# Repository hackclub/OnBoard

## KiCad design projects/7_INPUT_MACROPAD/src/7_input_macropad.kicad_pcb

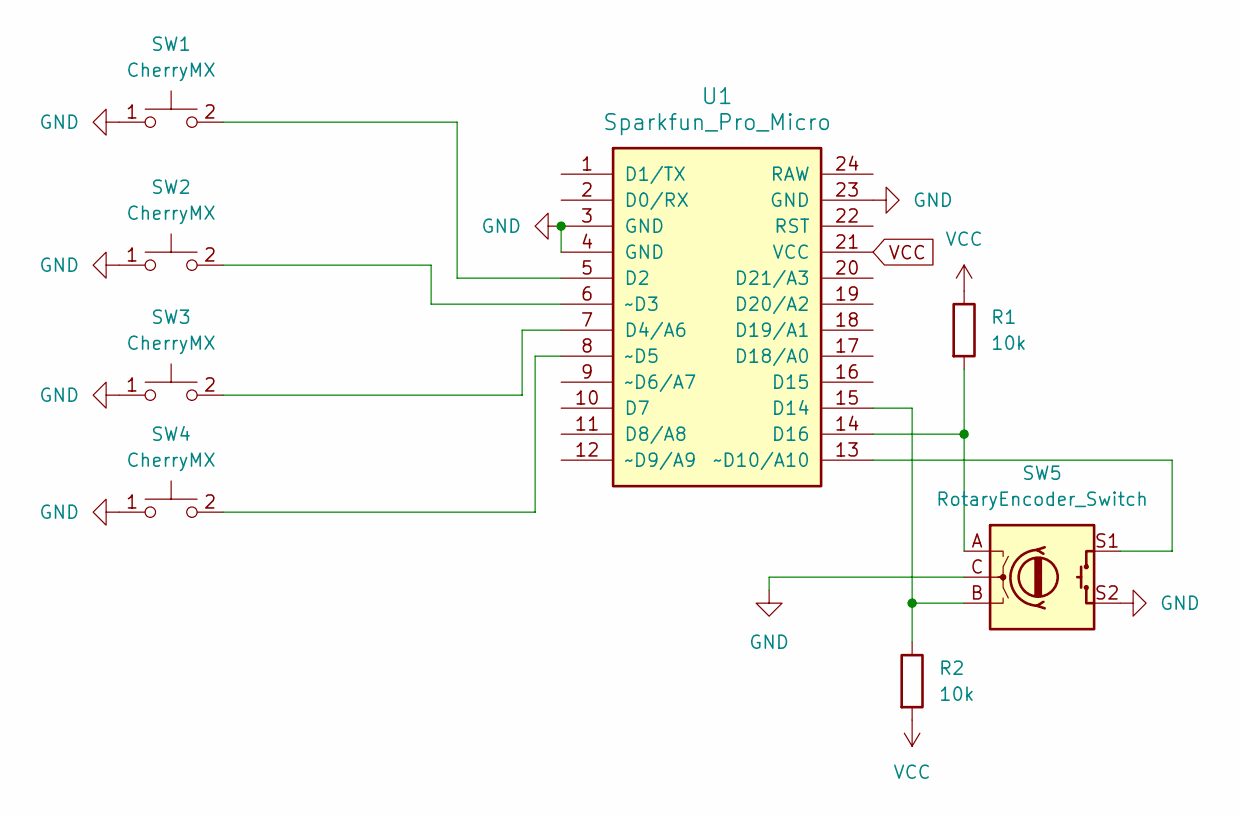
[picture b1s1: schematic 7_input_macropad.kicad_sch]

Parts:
R1, R2: 10k; R_0402_1005Metric
SW1, SW2, SW3, SW4: CherryMX; SW_Cherry_MX_1.00u_PCB
SW5: RotaryEncoder_Switch; RotaryEncoder_Alps_EC11E-Switch_Vertical_H20mm
U1: Sparkfun_Pro_Micro; ProMicro

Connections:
GND: SW1.1, SW2.1, SW3.1, SW4.1, SW5.C, SW5.S2, U1.3 (GND), U1.4 (GND), U1.23 (GND)
unnamed: SW1.2, U1.5 (D2)
unnamed: SW3.2, U1.7 (D4/A6)
unnamed: R2.1, SW5.B, U1.15 (D14)
unnamed: R1.2, SW5.A, U1.14 (D16)
unnamed: SW2.2, U1.6 (~D3)
unnamed: SW4.2, U1.8 (~D5)
unnamed: SW5.S1, U1.13 (~D10/A10)
VCC: R1.1, R2.2, U1.21 (VCC)

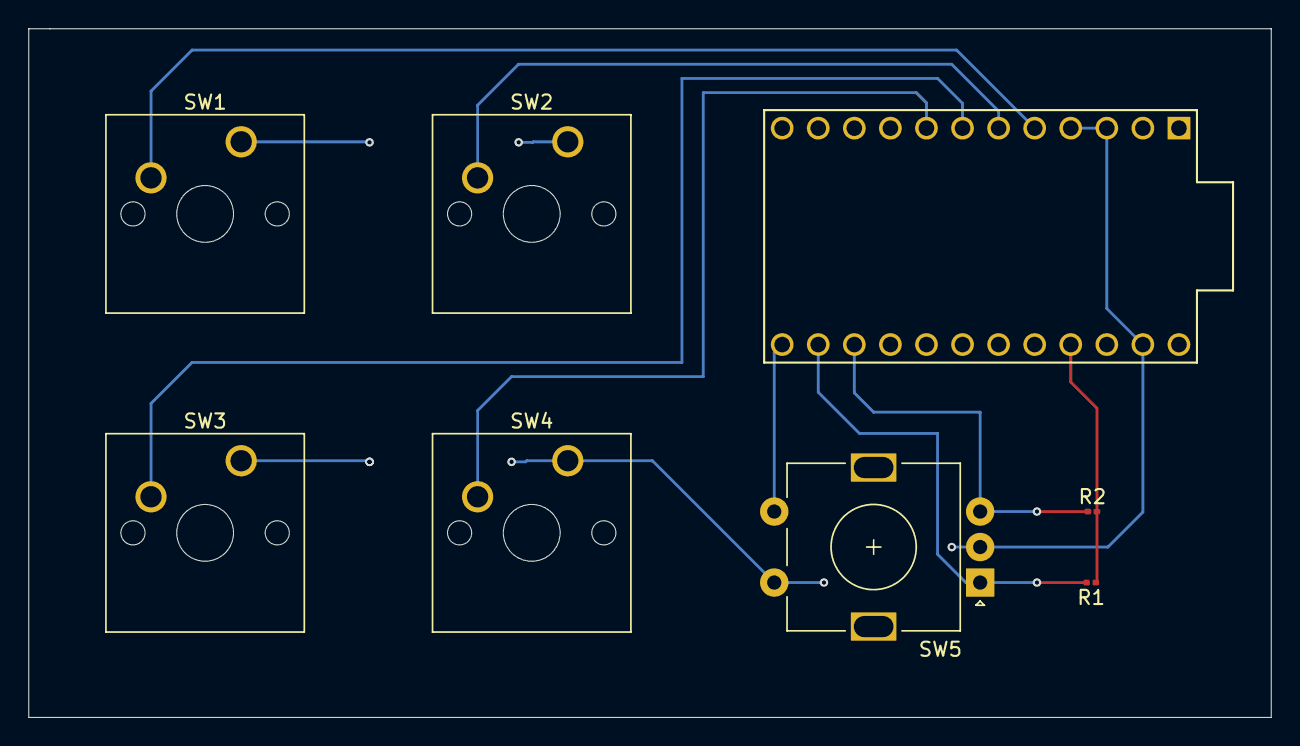
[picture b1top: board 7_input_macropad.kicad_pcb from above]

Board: 2 copper layers, 87.5 x 48.5 mm, 8 parts (0 on the bottom side), 9 nets.

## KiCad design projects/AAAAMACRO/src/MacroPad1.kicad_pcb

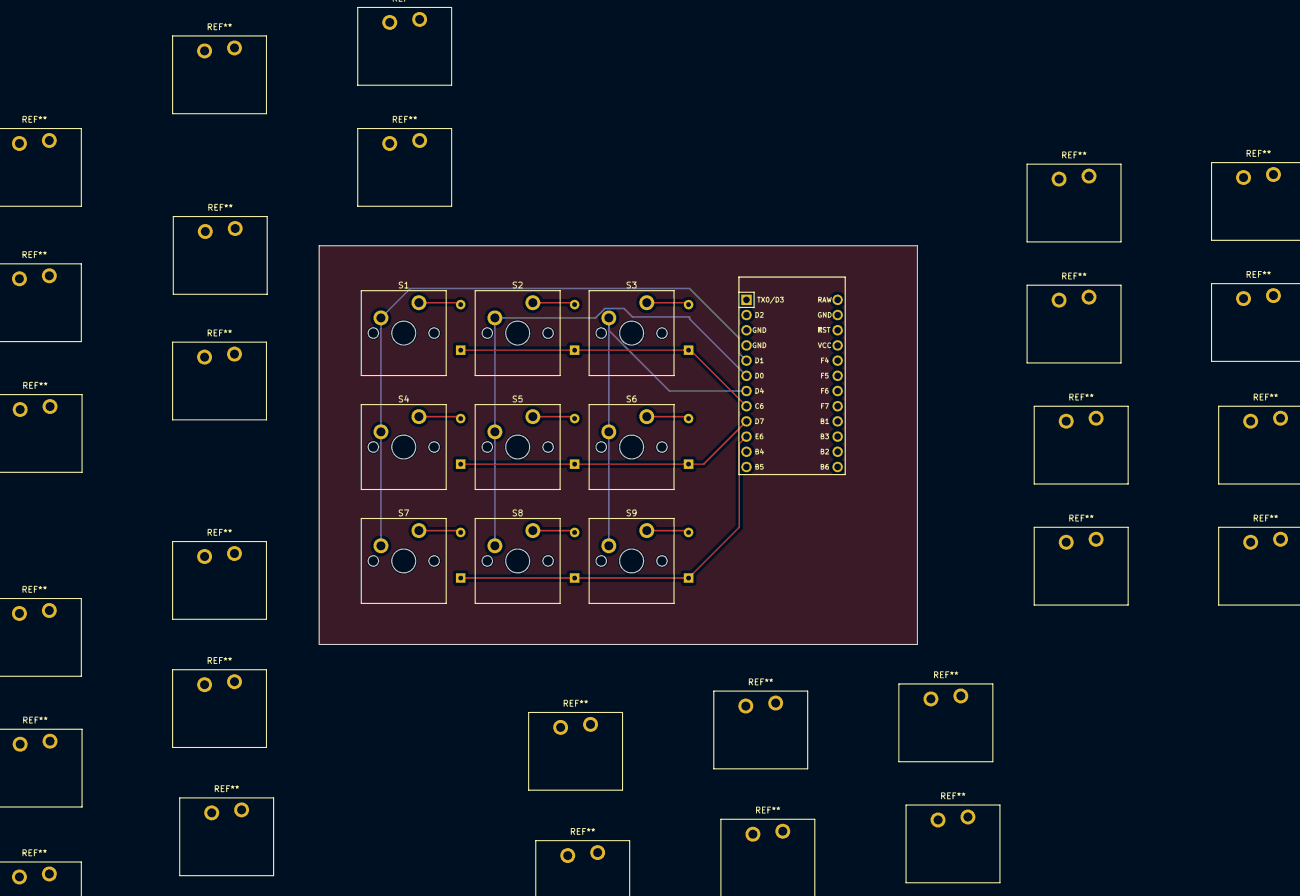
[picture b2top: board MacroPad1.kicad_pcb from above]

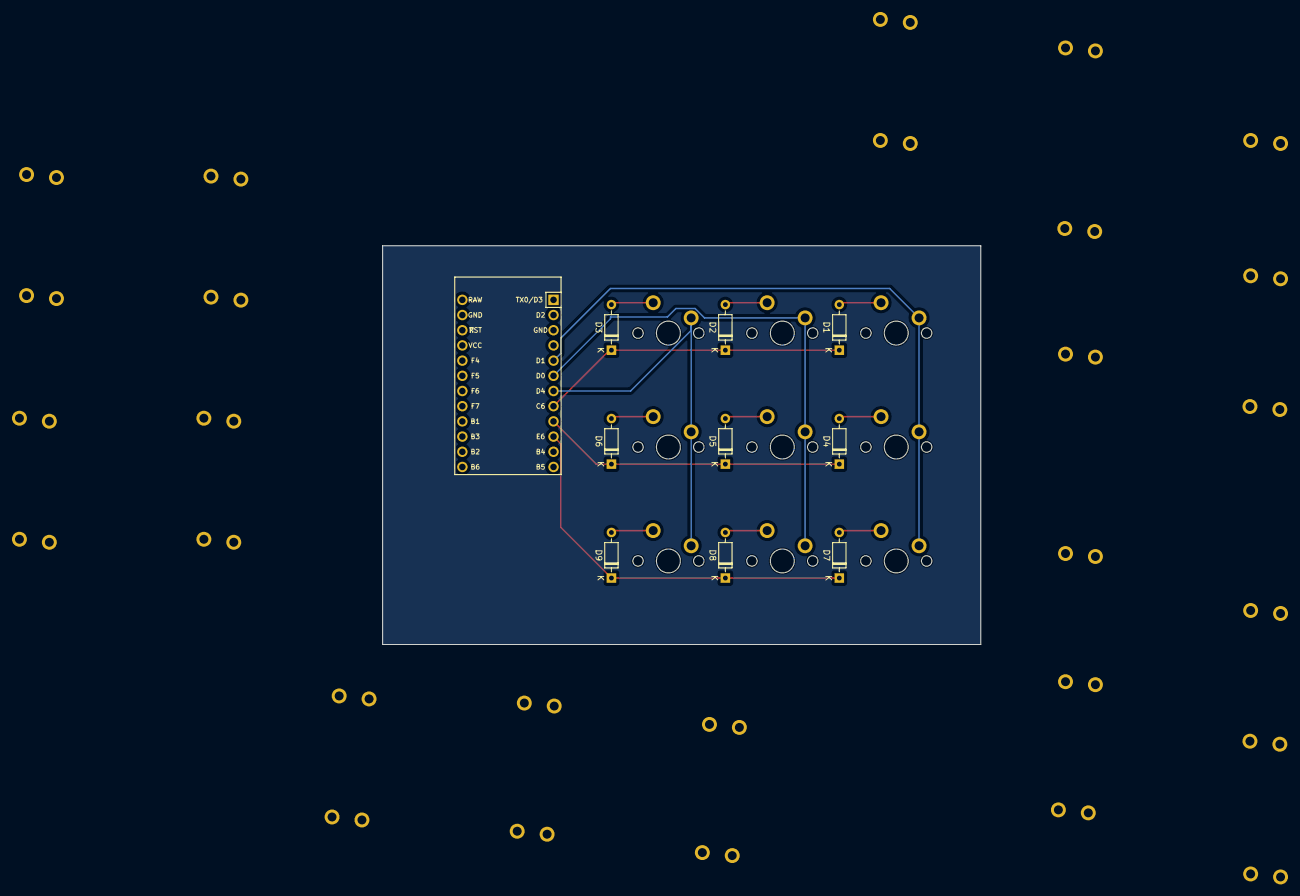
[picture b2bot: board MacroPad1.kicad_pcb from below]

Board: 2 copper layers, 100.0 x 66.7 mm, 19 parts (9 on the bottom side), 14 nets.

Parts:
D1, D2, D3, D4, D5, D6, D7, D8, D9: Diode; Diode_DO-35
S1, S2, S3, S4, S5, S6, S7, S8, S9: Keyswitch; MX_PCB_1.00u
U1: Arduino_Pro_Micro

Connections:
Column 0: S1.1, S2.1, S4.1, S5.1, S7.1, S8.1, U1.5 (2/PD1), U1.6 (3/PD0)
Column 2: S3.1, S6.1, S9.1, U1.7 (4/PD4)
unnamed: D1.2 (A), S1.2
unnamed: D2.2 (A), S2.2
unnamed: D3.2 (A), S3.2
unnamed: D4.2 (A), S4.2
unnamed: D5.2 (A), S5.2
unnamed: D6.2 (A), S6.2
unnamed: D7.2 (A), S7.2
unnamed: D8.2 (A), S8.2
unnamed: D9.2 (A), S9.2
Row 0: D1.1 (K), D2.1 (K), D3.1 (K), U1.8 (5/PC6)
Row 1: D4.1 (K), D5.1 (K), D6.1 (K), U1.9 (6/PD7)
Row 2: D7.1 (K), D8.1 (K), D9.1 (K), U1.10 (7/PE6)

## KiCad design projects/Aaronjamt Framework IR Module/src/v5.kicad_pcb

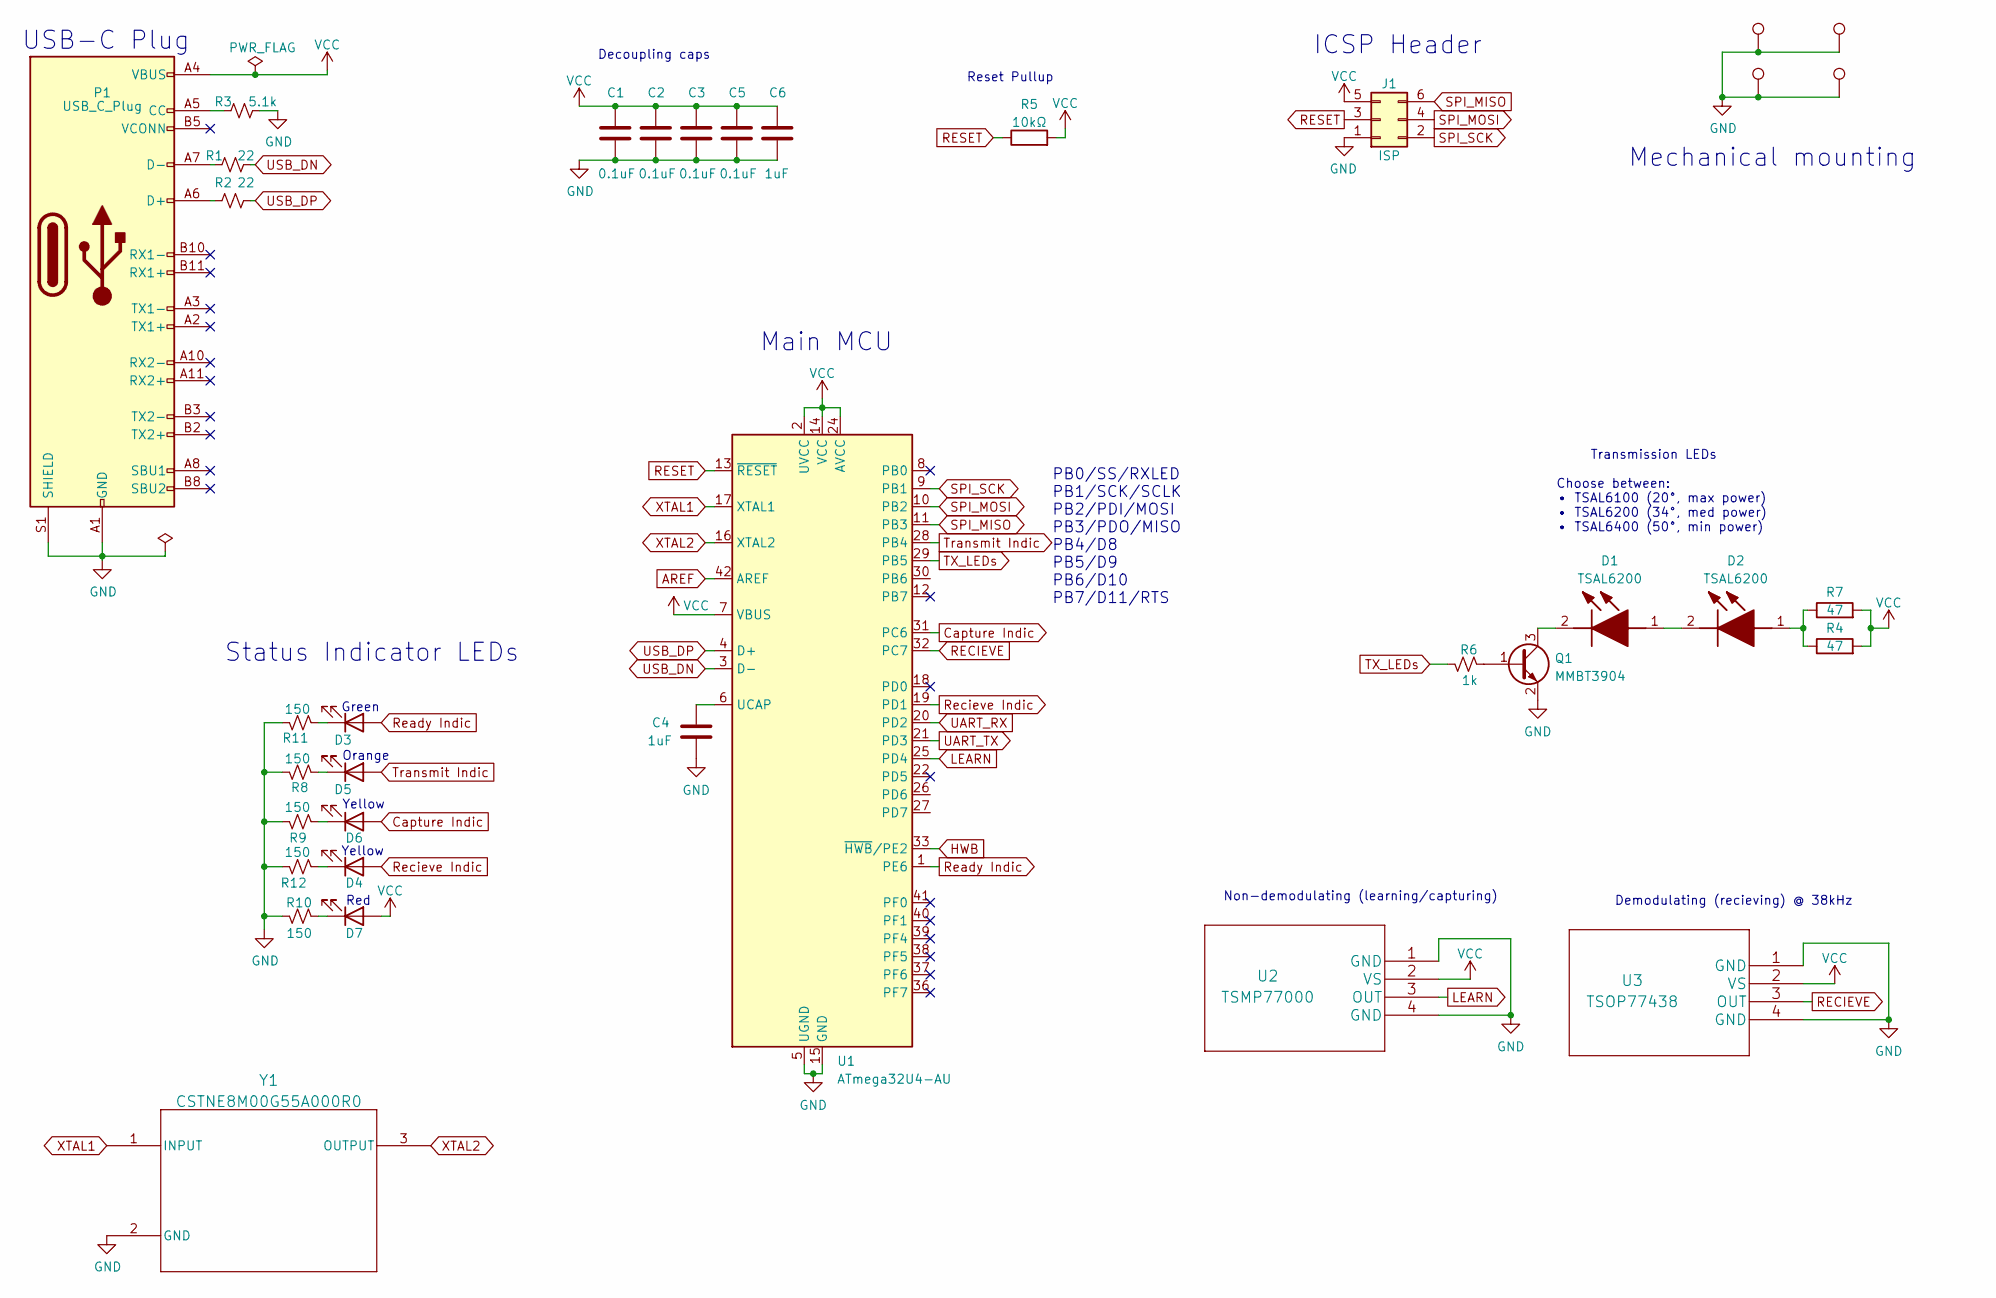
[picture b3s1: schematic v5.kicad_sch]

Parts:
C1, C2, C3, C5: 0.1uF; C_0603_1608Metric_Pad1.08x0.95mm_HandSolder
C4, C6: 1uF; C_0603_1608Metric_Pad1.08x0.95mm_HandSolder
D1, D2: TSAL6200; IN-S126ESGHIR; Manufacturer_Part_Number IN-S126ESGHIR
D3: LTST-C191KGKT; LED_0603_1608Metric_Pad1.05x0.95mm_HandSolder
D4, D6: LTST-C191KSKT; LED_0603_1608Metric_Pad1.05x0.95mm_HandSolder
D5: LTST-C191KFKT; LED_0603_1608Metric_Pad1.05x0.95mm_HandSolder
D7: LTST-C191KRKT; LED_0603_1608Metric_Pad1.05x0.95mm_HandSolder
J1: ISP; PinHeader_2x03_P2.54mm_Vertical
P1: USB_C_Plug; USB_C_Plug_Molex_105444
Q1: MMBT3904; SOT-23
R1, R2: 22; R_0603_1608Metric_Pad0.98x0.95mm_HandSolder
R3: 5.1k; R_0603_1608Metric_Pad0.98x0.95mm_HandSolder
R4, R7: 47; R_0603_1608Metric_Pad0.98x0.95mm_HandSolder
R5: 10kΩ; R_0603_1608Metric_Pad0.98x0.95mm_HandSolder
R6: 1k; R_0603_1608Metric_Pad0.98x0.95mm_HandSolder
R8, R9, R11, R12: 150; R_0603_1608Metric_Pad0.98x0.95mm_HandSolder
R10: 150; R_0603_1608Metric_Pad0.98x0.95mm_HandSolder; Part SDR03EZPJ151
TP1, TP2, TP3, TP4: TestPoint; TestPoint_Pad_1.5x1.5mm
U1: ATmega32U4-AU; TQFP-44_10x10mm_P0.8mm
U2: TSMP77000; Vishay_Heimdall_90
U3: TSOP77438; Vishay_Heimdall_90
Y1: CSTNE8M00G55A000R0; RESONATOR_00G55A000R0_MUR

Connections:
AREF: U1.42 (AREF)
Capture Indic: D6.2 (A), U1.31 (PC6)
GND: C1.2, C2.2, C3.2, C4.2, C5.2, C6.2, J1.1, P1.A1 (GND), P1.A12 (GND), P1.B1 (GND), P1.B12 (GND), P1.S1 (SHIELD), Q1.2 (E), R3.2, R8.1, R9.1, R10.1, R11.1, R12.1, TP1.1, TP2.1, TP3.1, TP4.1, U1.5 (UGND), U1.15 (GND), U1.23 (GND), U1.35 (GND), U1.43 (GND), U2.1 (GND), U2.4 (GND), U3.1 (GND), U3.4 (GND), Y1.2 (GND)
HWB: U1.33 (~HWB/PE2)
LEARN: U1.25 (PD4), U2.3 (OUT)
unnamed: D1.1 (A), D2.2 (K)
unnamed: D1.2 (K), Q1.3 (C)
unnamed: D2.1 (A), R4.1, R7.1
unnamed: D3.1 (K), R11.2
unnamed: D4.1 (K), R12.2
unnamed: D5.1 (K), R8.2
unnamed: D6.1 (K), R9.2
unnamed: D7.1 (K), R10.2
unnamed: P1.A5 (CC), R3.1
unnamed: P1.A6 (D+), R2.1
unnamed: P1.A7 (D-), R1.1
unnamed: Q1.1 (B), R6.2
unnamed: C4.1, U1.6 (UCAP)
RECIEVE: U1.32 (PC7), U3.3 (OUT)
RESET: J1.3, R5.1, U1.13 (~RESET)
Ready Indic: D3.2 (A), U1.1 (PE6)
Recieve Indic: D4.2 (A), U1.19 (PD1)
SPI_MISO: J1.6, U1.11 (PB3)
SPI_MOSI: J1.4, U1.10 (PB2)
SPI_SCK: J1.2, U1.9 (PB1)
TX_LEDs: R6.1, U1.29 (PB5)
Transmit Indic: D5.2 (A), U1.28 (PB4)
UART_RX: U1.20 (PD2)
UART_TX: U1.21 (PD3)
USB_DN: R1.2, U1.3 (D-)
USB_DP: R2.2, U1.4 (D+)
VCC: C1.1, C2.1, C3.1, C5.1, C6.1, D7.2 (A), J1.5, P1.A4 (VBUS), P1.A9 (VBUS), P1.B4 (VBUS), P1.B9 (VBUS), R4.2, R5.2, R7.2, U1.2 (UVCC), U1.7 (VBUS), U1.14 (VCC), U1.24 (AVCC), U1.34 (VCC), U1.44 (AVCC), U2.2 (VS), U3.2 (VS)
XTAL1: U1.17 (XTAL1), Y1.1 (INPUT)
XTAL2: U1.16 (XTAL2), Y1.3 (OUTPUT)

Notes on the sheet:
Mechanical mounting
Orange
Green
Yellow
PB0/SS/RXLED PB1/SCK/SCLK PB2/PDI/MOSI PB3/PDO/MISO PB4/D8 PB5/D9 PB6/D10 PB7/D11/RTS
USB-C Plug
Status Indicator LEDs
Red
Main MCU
Transmission LEDs Choose between: • TSAL6100 (20°, max power) • TSAL6200 (34°, med power) • TSAL6400 (50°, min power)
Non-demodulating (learning/capturing)
ICSP Header
Reset Pullup
Demodulating (recieving) @ 38kHz
Decoupling caps

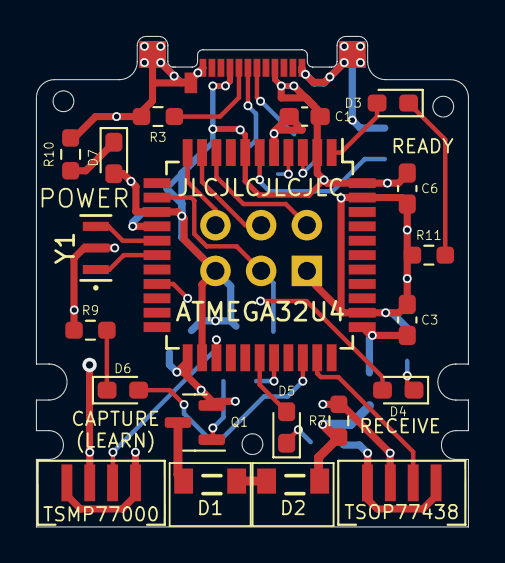
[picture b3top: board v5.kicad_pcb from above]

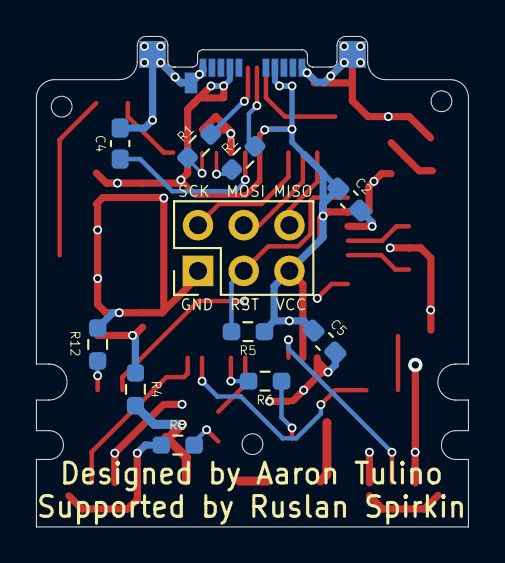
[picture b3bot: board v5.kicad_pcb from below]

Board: 4 copper layers, 24.0 x 27.2 mm, 36 parts (13 on the bottom side), 30 nets.

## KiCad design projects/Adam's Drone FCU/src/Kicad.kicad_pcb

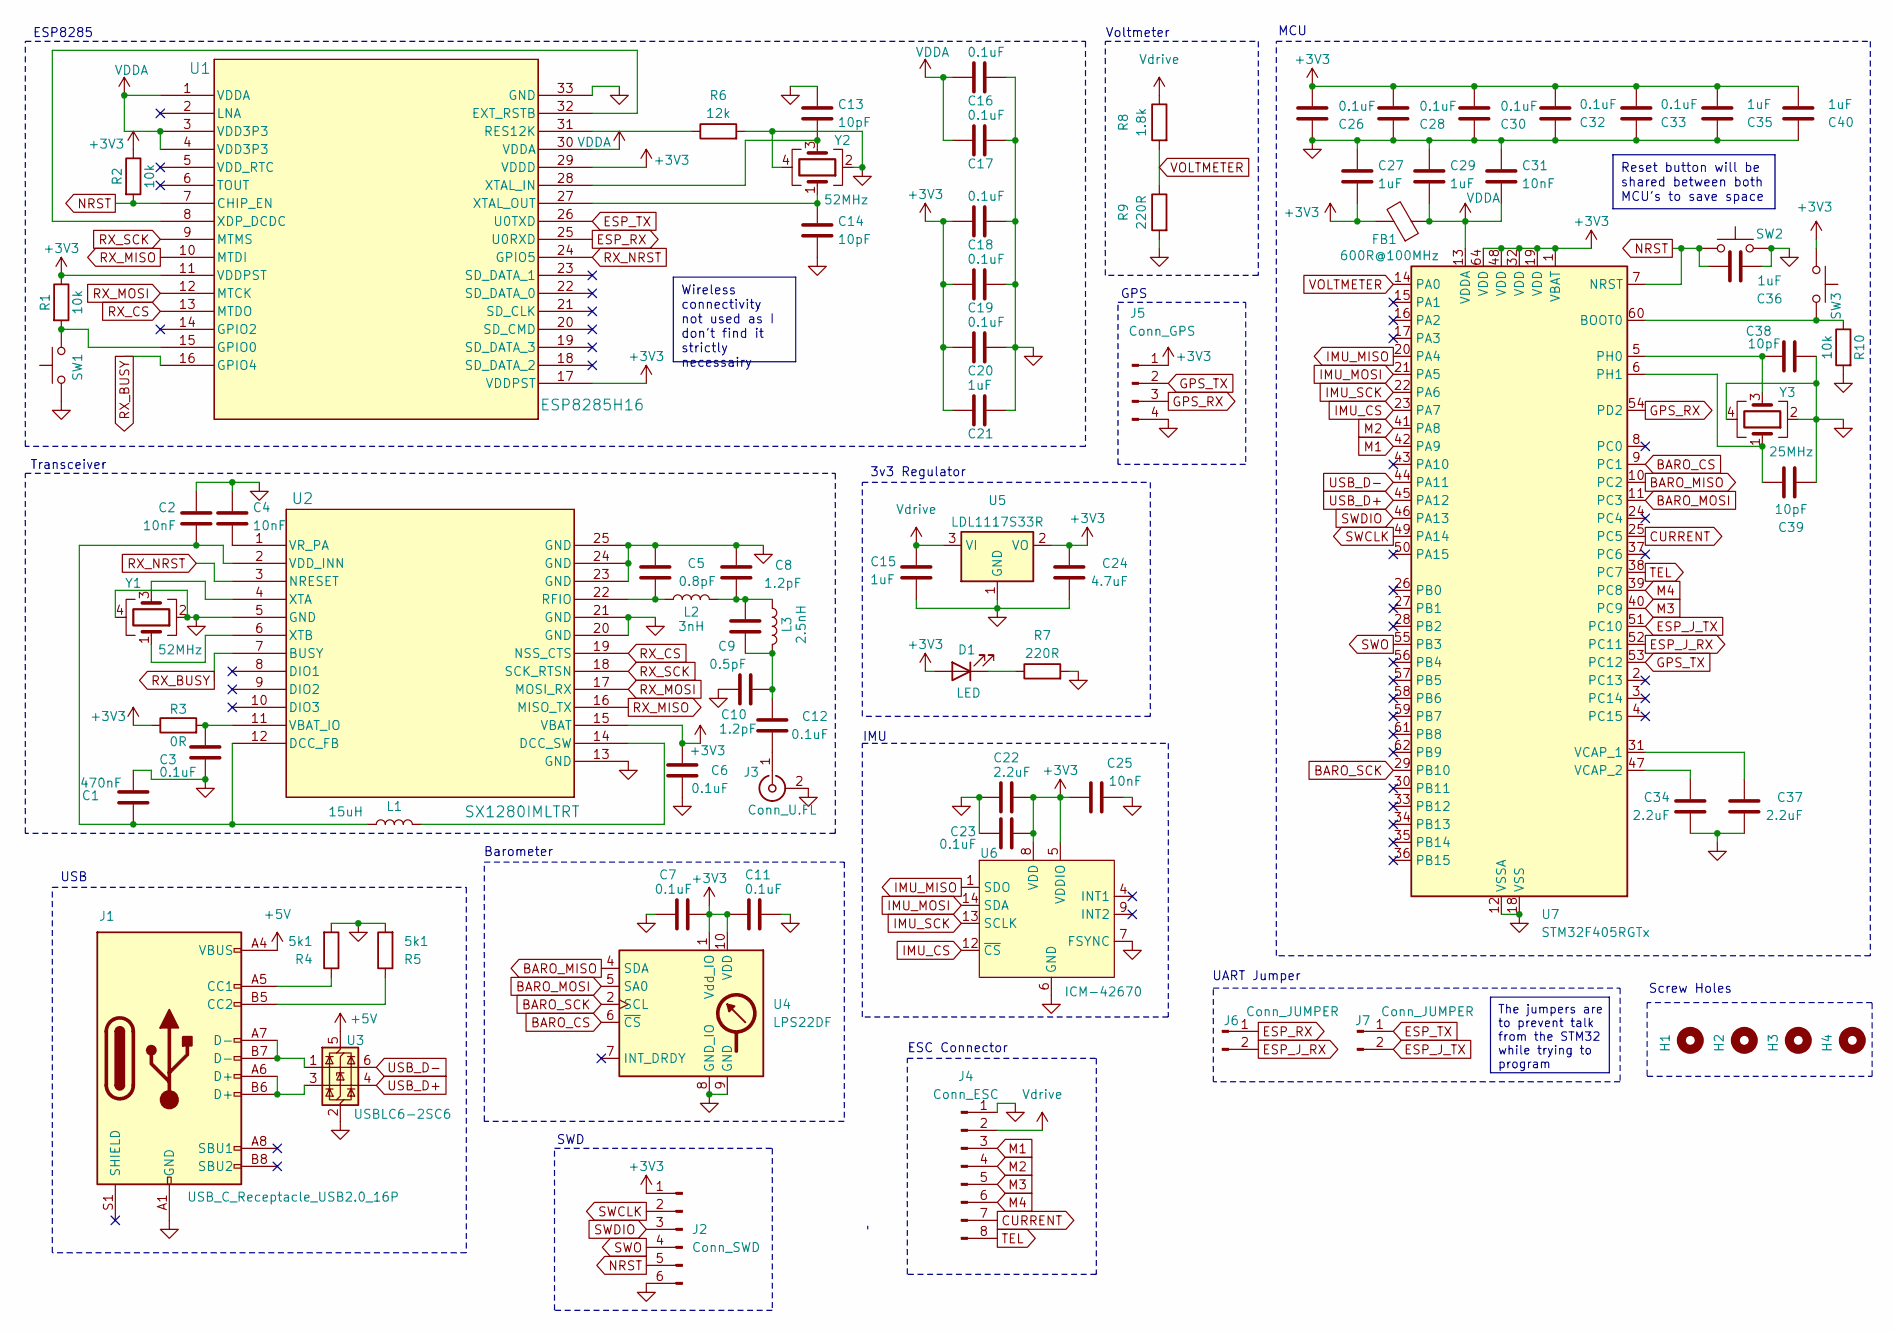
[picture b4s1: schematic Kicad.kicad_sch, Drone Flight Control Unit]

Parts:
C1: 470nF; C_0402_1005Metric
C2, C4, C25, C31: 10nF; C_0402_1005Metric
C3, C6, C7, C11, C12, C16, C17, C18, C19, C20, C23, C26, C28, C30, C32, C33: 0.1uF; C_0402_1005Metric
C5: 0.8pF; C_0402_1005Metric
C8, C10: 1.2pF; C_0402_1005Metric
C9: 0.5pF; C_0402_1005Metric
C13, C14, C38, C39: 10pF; C_0402_1005Metric
C15, C21, C27, C29, C35, C36, C40: 1uF; C_0402_1005Metric
C22, C34, C37: 2.2uF; C_0402_1005Metric
C24: 4.7uF; C_0402_1005Metric
D1: LED; LED_0603_1608Metric; MPN C598257; LCSC C598257
FB1: 600R@100MHz; L_0805_2012Metric; MPN C304318
H1, H2, H3, H4: MountingHole; MountingHole_4mm_Pad
J1: USB_C_Receptacle_USB2.0_16P; USB_C_Receptacle_GCT_USB4105-xx-A_16P_TopMnt_Horizontal; MPN C2988369; LCSC C2988369
J2: Conn_SWD; PinHeader_2x03_P2.54mm_Vertical; MPN C77761; LCSC C77761
J3: Conn_U.FL; CONN1_CONUFL_TEC; MPN C5137195; LCSC C5137195
J4: Conn_ESC; JST_SHL_SM08B-SHLS-TF_1x08-1MP_P1.00mm_Horizontal
J5: Conn_GPS; SolderWire-0.1sqmm_1x04_P3.6mm_D0.4mm_OD1mm
J6, J7: Conn_JUMPER; PinHeader_1x02_P2.54mm_Vertical; MPN C3336192; LCSC C3336192
L1: 15uH; L_0805_2012Metric
L2: 3nH; L_0402_1005Metric
L3: 2.5nH; L_0402_1005Metric; MPN C5607159
R1, R2, R10: 10k; R_0402_1005Metric
R3: 0R; R_0402_1005Metric
R4, R5: 5k1; R_0402_1005Metric
R6: 12k; R_0402_1005Metric
R7, R9: 220R; R_0402_1005Metric
R8: 1.8k; R_0402_1005Metric
SW1, SW2, SW3: SW_Push; EVQ_P7_PAN; MPN C2888430
U1: ESP8285H16; QFN-32-1EP_5x5mm_P0.5mm_EP3.7x3.7mm_ThermalVias; MPN C967019; LCSC C967019
U2: SX1280IMLTRT; QFN-24-1EP_4x4mm_P0.5mm_EP2.75x2.75mm_ThermalVias; LCSC C125969
U3: USBLC6-2SC6; SOT-23-6; MPN C7519; LCSC C7519
U4: LPS22DF; ST_HLGA-10_2x2mm_P0.5mm_LayoutBorder3x2y; MPN C3253714; LCSC C3253714
U5: LDL1117S33R; SOT-223-3_TabPin2; MPN C435835; LCSC C435835
U6: ICM-42670; LGA-14_3x2.5mm_P0.5mm_LayoutBorder3x4y; MPN C3288646; LCSC C3288646
U7: STM32F405RGTx; LQFP-64_10x10mm_P0.5mm; MPN C15742; LCSC C15742
Y1, Y2: 52MHz; Crystal_SMD_3225-4Pin_3.2x2.5mm
Y3: 25MHz; Crystal_SMD_2016-4Pin_2.0x1.6mm

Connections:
+3V3: C6.1, C7.2, C11.1, C18.2, C19.2, C20.2, C21.2, C22.2, C23.2, C24.1, C25.1, C26.2, C27.2, C28.2, C30.2, C32.2, C33.2, C35.2, C40.2, D1.2 (A), FB1.2, J2.1, J5.1, R1.1, R2.1, R3.1, SW3.1, U1.11 (VDDPST), U1.17 (VDDPST), U1.29 (VDDD), U2.15 (VBAT), U4.1 (Vdd_IO), U4.10 (VDD), U5.2 (VO), U6.5 (VDDIO), U6.8 (VDD), U7.1 (VBAT), U7.19 (VDD), U7.32 (VDD), U7.48 (VDD), U7.64 (VDD)
+5V: J1.A4 (VBUS), J1.A9 (VBUS), J1.B4 (VBUS), J1.B9 (VBUS), U3.5 (VBUS)
BARO_CS: U4.6 (~CS), U7.9 (PC1)
BARO_MISO: U4.4 (SDA), U7.10 (PC2)
BARO_MOSI: U4.5 (SA0), U7.11 (PC3)
BARO_SCK: U4.2 (SCL), U7.29 (PB10)
CURRENT: J4.7, U7.25 (PC5)
ESP_J_RX: J6.2, U7.52 (PC11)
ESP_J_TX: J7.2, U7.51 (PC10)
ESP_RX: J6.1, U1.25 (U0RXD)
ESP_TX: J7.1, U1.26 (U0TXD)
GND: C1.2, C2.1, C3.2, C4.1, C5.1, C6.2, C7.1, C8.2, C10.2, C11.2, C13.1, C14.2, C15.2, C16.1, C17.1, C18.1, C19.1, C20.1, C21.1, C22.1, C23.1, C24.2, C25.2, C26.1, C27.1, C28.1, C29.1, C30.1, C31.1, C32.1, C33.1, C34.2, C35.1, C36.1, C37.2, C38.1, C39.1, C40.1, J1.A1 (GND), J1.A12 (GND), J1.B1 (GND), J1.B12 (GND), J2.6, J3.2 (Ext), J4.1, J5.4, R4.2, R5.2, R6.2, R7.2, R9.2, R10.2, SW1.1, SW2.1, U1.33 (GND), U2.5 (GND), U2.13 (GND), U2.20 (GND), U2.21 (GND), U2.23 (GND), U2.24 (GND), U2.25 (GND), U3.2 (GND), U4.3 (GND), U4.8 (GND_IO), U4.9 (GND), U5.1 (GND), U6.6 (GND), U6.7 (FSYNC), U7.12 (VSSA), U7.18 (VSS), U7.63 (VSS), Y1.2, Y1.4, Y2.2, Y2.4, Y3.2, Y3.4
GPS_RX: J5.3, U7.54 (PD2)
GPS_TX: J5.2, U7.53 (PC12)
IMU_CS: U6.12 (~CS), U7.23 (PA7)
IMU_MISO: U6.1 (SDO), U7.20 (PA4)
IMU_MOSI: U6.14 (SDA), U7.21 (PA5)
IMU_SCK: U6.13 (SCLK), U7.22 (PA6)
M1: J4.3, U7.42 (PA9)
M2: J4.4, U7.41 (PA8)
M3: J4.5, U7.40 (PC9)
M4: J4.6, U7.39 (PC8)
NRST: C36.2, J2.5, R2.2, SW2.2, U1.7 (CHIP_EN), U7.7 (NRST)
unnamed: C8.1, C9.2, L2.2, L3.1
unnamed: C9.1, C10.1, C12.2, L3.2
unnamed: D1.1 (K), R7.1
unnamed: J1.A5 (CC1), R4.1
unnamed: J1.B5 (CC2), R5.1
unnamed: J1.A6 (D+), J1.B6 (D+), U3.3 (I/O2)
unnamed: J1.A7 (D-), J1.B7 (D-), U3.1 (I/O1)
unnamed: C12.1, J3.1 (In)
unnamed: U1.8 (XDP_DCDC), U1.32 (EXT_RSTB)
unnamed: R1.2, SW1.2, U1.15 (GPIO0)
unnamed: R6.1, U1.31 (RES12K)
unnamed: C13.2, U1.28 (XTAL_IN), Y2.3
unnamed: C14.1, U1.27 (XTAL_OUT), Y2.1
unnamed: C1.1, C2.2, L1.1, U2.2 (VDD_INN), U2.12 (DCC_FB)
unnamed: L1.2, U2.14 (DCC_SW)
unnamed: C5.2, L2.1, U2.22 (RFIO)
unnamed: C3.1, R3.2, U2.11 (VBAT_IO)
unnamed: C4.2, U2.1 (VR_PA)
unnamed: U2.4 (XTA), Y1.3
unnamed: U2.6 (XTB), Y1.1
unnamed: R10.1, SW3.2, U7.60 (BOOT0)
unnamed: C38.2, U7.5 (PH0), Y3.3
unnamed: C39.2, U7.6 (PH1), Y3.1
unnamed: C37.1, U7.31 (VCAP_1)
unnamed: C34.1, U7.47 (VCAP_2)
RX_BUSY: U1.16 (GPIO4), U2.7 (BUSY)
RX_CS: U1.13 (MTDO), U2.19 (NSS_CTS)
RX_MISO: U1.10 (MTDI), U2.16 (MISO_TX)
RX_MOSI: U1.12 (MTCK), U2.17 (MOSI_RX)
RX_NRST: U1.24 (GPIO5), U2.3 (NRESET)
RX_SCK: U1.9 (MTMS), U2.18 (SCK_RTSN)
SWCLK: J2.2, U7.49 (PA14)
SWDIO: J2.3, U7.46 (PA13)
SWO: J2.4, U7.55 (PB3)
TEL: J4.8, U7.38 (PC7)
USB_D+: U3.4 (I/O2), U7.45 (PA12)
USB_D-: U3.6 (I/O1), U7.44 (PA11)
VDDA: C16.2, C17.2, C29.2, C31.2, FB1.1, U1.1 (VDDA), U1.3 (VDD3P3), U1.4 (VDD3P3), U1.30 (VDDA), U7.13 (VDDA)
VOLTMETER: R8.2, R9.1, U7.14 (PA0)
Vdrive: C15.1, J4.2, R8.1, U5.3 (VI)

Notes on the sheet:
Reset button will be shared between both MCU's to save space
The jumpers are to prevent talk from the STM32 while trying to program
Wireless connectivity not used as I don't find it strictly necessairy
MCU
Barometer
UART Jumper
3v3 Regulator
Voltmeter
ESP8285
Screw Holes
USB
Transceiver
SWD
ESC Connector
IMU
GPS

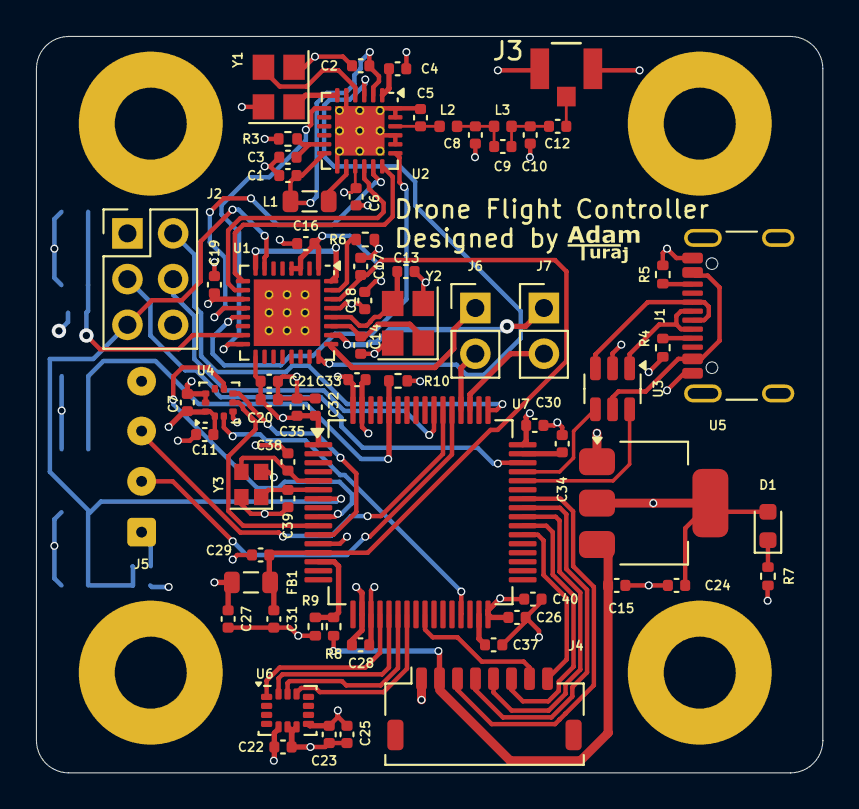
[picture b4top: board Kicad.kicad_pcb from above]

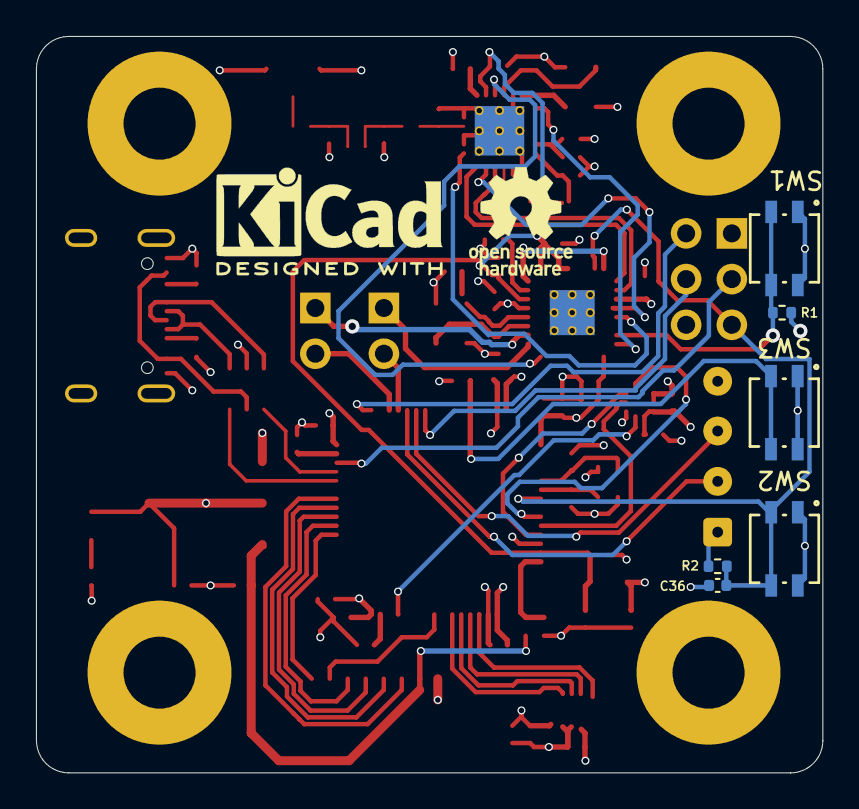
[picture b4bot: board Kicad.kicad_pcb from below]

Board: 4 copper layers, 43.7 x 40.9 mm, 79 parts (6 on the bottom side), 63 nets.

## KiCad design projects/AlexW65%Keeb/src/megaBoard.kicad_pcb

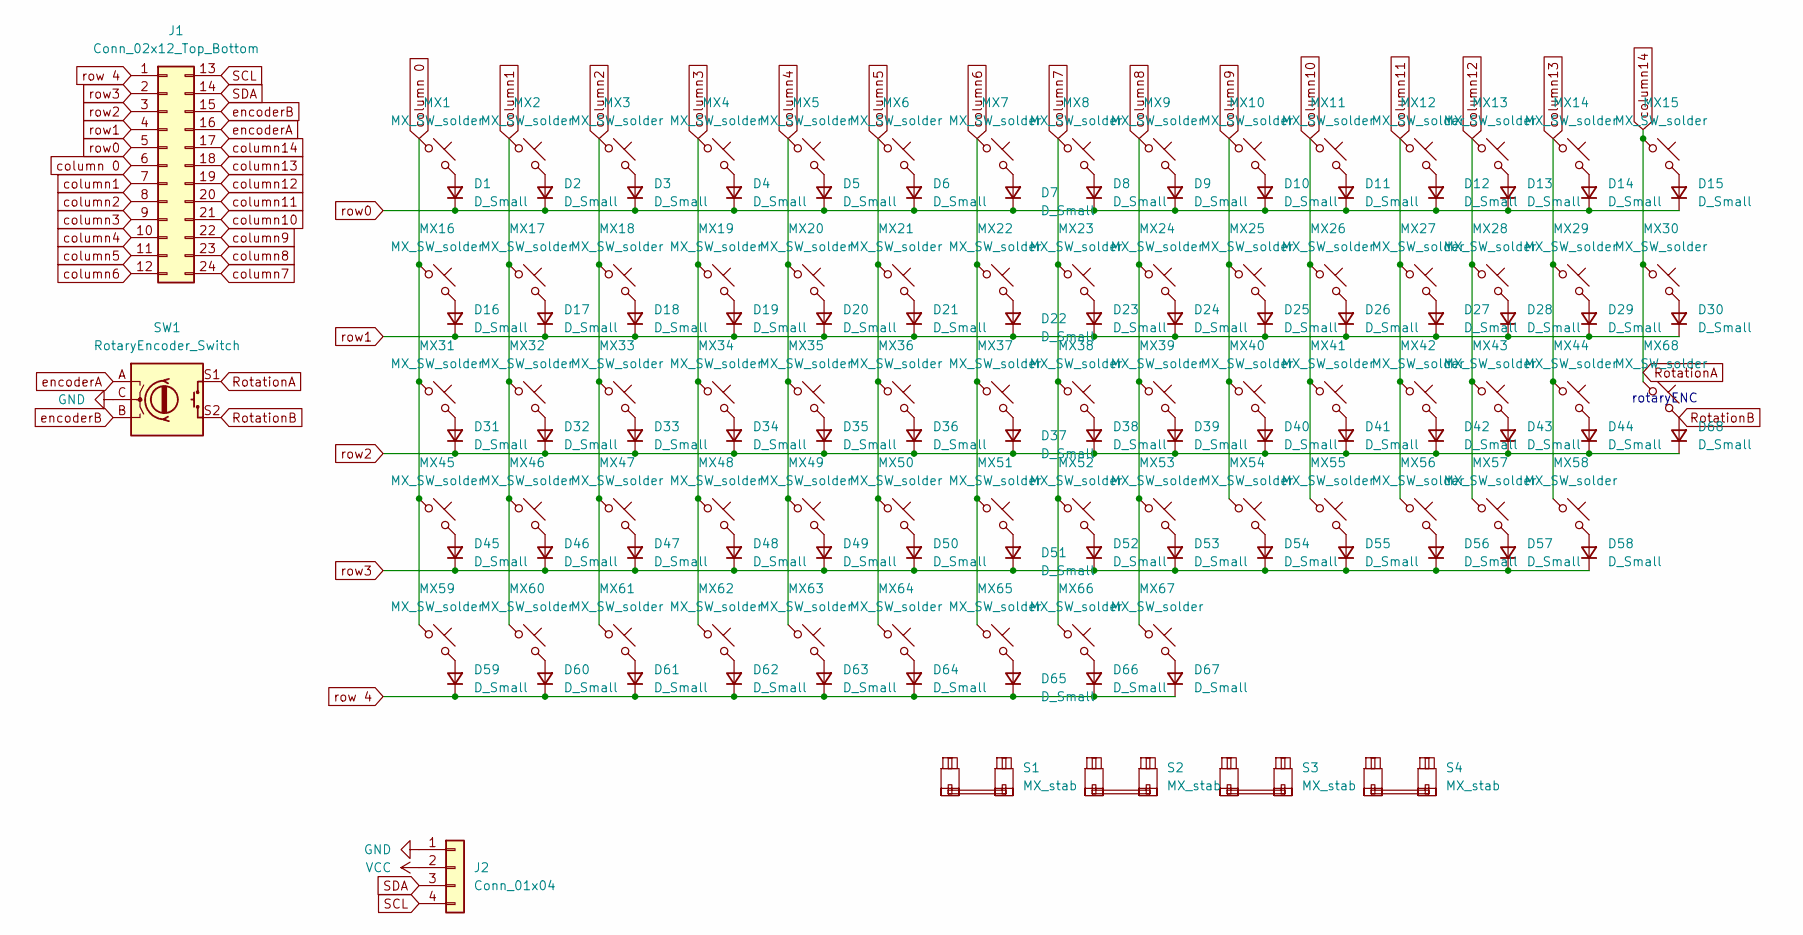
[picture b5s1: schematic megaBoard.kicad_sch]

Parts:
D1, D2, D3, D4, D5, D6, D7, D8, D9, D10, D11, D12, D13, D14, D15, D16, D17, D18, D19, D20, D21, D22, D23, D24, D25, D26, D27, D28, D29, D30, D31, D32, D33, D34, D35, D36, D37, D38, D39, D40, D41, D42, D43, D44, D45, D46, D47, D48, D49, D50, D51, D52, D53, D54, D55, D56, D57, D58, D59, D60, D61, D62, D63, D64, D65, D66, D67, D68: D_Small; D_SOD-123
J1: Conn_02x12_Top_Bottom; ProMicro_USBdn
J2: Conn_01x04; PinHeader_1x04_P2.54mm_Vertical
MX1, MX2, MX3, MX4, MX5, MX6, MX7, MX8, MX9, MX10, MX11, MX12, MX13, MX14, MX15, MX17, MX18, MX19, MX20, MX21, MX22, MX23, MX24, MX25, MX26, MX27, MX28, MX30, MX32, MX33, MX34, MX35, MX36, MX37, MX38, MX39, MX40, MX41, MX42, MX43, MX44, MX45, MX46, MX47, MX48, MX49, MX50, MX51, MX52, MX53, MX54, MX55, MX57, MX58, MX62, MX65, MX66, MX67, MX68: MX_SW_solder; SW_MX_1u
MX16, MX29: MX_SW_solder; SW_MX_1.5u
MX31, MX59, MX60, MX61, MX63, MX64: MX_SW_solder; SW_MX_1.25u
MX56: MX_SW_solder; SW_MX_1.75u
S1: MX_stab; STAB_MX_P_2u
S2, S3: MX_stab; STAB_MX_P_2.25u
S4: MX_stab; STAB_MX_P_6.25u
SW1: RotaryEncoder_Switch; RotaryEncoder_EC11

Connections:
GND: J2.1, SW1.C
unnamed: D1.2 (A), MX1.2
unnamed: D2.2 (A), MX2.2
unnamed: D3.2 (A), MX3.2
unnamed: D4.2 (A), MX4.2
unnamed: D5.2 (A), MX5.2
unnamed: D6.2 (A), MX6.2
unnamed: D7.2 (A), MX7.2
unnamed: D8.2 (A), MX8.2
unnamed: D9.2 (A), MX9.2
unnamed: D10.2 (A), MX10.2
unnamed: D11.2 (A), MX11.2
unnamed: D12.2 (A), MX12.2
unnamed: D13.2 (A), MX13.2
unnamed: D14.2 (A), MX14.2
unnamed: D15.2 (A), MX15.2
unnamed: D16.2 (A), MX16.2
unnamed: D17.2 (A), MX17.2
unnamed: D18.2 (A), MX18.2
unnamed: D19.2 (A), MX19.2
unnamed: D20.2 (A), MX20.2
unnamed: D21.2 (A), MX21.2
unnamed: D22.2 (A), MX22.2
unnamed: D23.2 (A), MX23.2
unnamed: D24.2 (A), MX24.2
unnamed: D25.2 (A), MX25.2
unnamed: D26.2 (A), MX26.2
unnamed: D27.2 (A), MX27.2
unnamed: D28.2 (A), MX28.2
unnamed: D29.2 (A), MX29.2
unnamed: D30.2 (A), MX30.2
unnamed: D31.2 (A), MX31.2
unnamed: D32.2 (A), MX32.2
unnamed: D33.2 (A), MX33.2
unnamed: D34.2 (A), MX34.2
unnamed: D35.2 (A), MX35.2
unnamed: D36.2 (A), MX36.2
unnamed: D37.2 (A), MX37.2
unnamed: D38.2 (A), MX38.2
unnamed: D39.2 (A), MX39.2
unnamed: D40.2 (A), MX40.2
unnamed: D41.2 (A), MX41.2
unnamed: D42.2 (A), MX42.2
unnamed: D43.2 (A), MX43.2
unnamed: D44.2 (A), MX44.2
unnamed: D45.2 (A), MX45.2
unnamed: D46.2 (A), MX46.2
unnamed: D47.2 (A), MX47.2
unnamed: D48.2 (A), MX48.2
unnamed: D49.2 (A), MX49.2
unnamed: D50.2 (A), MX50.2
unnamed: D51.2 (A), MX51.2
unnamed: D52.2 (A), MX52.2
unnamed: D53.2 (A), MX53.2
unnamed: D54.2 (A), MX54.2
unnamed: D55.2 (A), MX55.2
unnamed: D56.2 (A), MX56.2
unnamed: D57.2 (A), MX57.2
unnamed: D58.2 (A), MX58.2
unnamed: D59.2 (A), MX59.2
unnamed: D60.2 (A), MX60.2
unnamed: D61.2 (A), MX61.2
unnamed: D62.2 (A), MX62.2
unnamed: D63.2 (A), MX63.2
unnamed: D64.2 (A), MX64.2
unnamed: D65.2 (A), MX65.2
unnamed: D66.2 (A), MX66.2
unnamed: D67.2 (A), MX67.2
RotationA: J1.17, MX15.1, MX30.1, MX68.1, SW1.S1
RotationB: D68.2 (A), MX68.2, SW1.S2
SCL: J1.13, J2.4
SDA: J1.14, J2.3
VCC: J2.2
column1: J1.7, MX2.1, MX17.1, MX32.1, MX46.1, MX60.1
column2: J1.8, MX3.1, MX18.1, MX33.1, MX47.1, MX61.1
column3: J1.9, MX4.1, MX19.1, MX34.1, MX48.1, MX62.1
column4: J1.10, MX5.1, MX20.1, MX35.1, MX49.1, MX63.1
column5: J1.11, MX6.1, MX21.1, MX36.1, MX50.1, MX64.1
column6: J1.12, MX7.1, MX22.1, MX37.1, MX51.1, MX65.1
column7: J1.24, MX8.1, MX23.1, MX38.1, MX52.1, MX66.1
column8: J1.23, MX9.1, MX24.1, MX39.1, MX53.1, MX67.1
column9: J1.22, MX10.1, MX25.1, MX40.1, MX54.1
column10: J1.21, MX11.1, MX26.1, MX41.1, MX55.1
column11: J1.20, MX12.1, MX27.1, MX42.1, MX56.1
column12: J1.19, MX13.1, MX28.1, MX43.1, MX57.1
column13: J1.18, MX14.1, MX29.1, MX44.1, MX58.1
column 0: J1.6, MX1.1, MX16.1, MX31.1, MX45.1, MX59.1
encoderA: J1.16, SW1.A
encoderB: J1.15, SW1.B
row0: D1.1 (K), D2.1 (K), D3.1 (K), D4.1 (K), D5.1 (K), D6.1 (K), D7.1 (K), D8.1 (K), D9.1 (K), D10.1 (K), D11.1 (K), D12.1 (K), D13.1 (K), D14.1 (K), D15.1 (K), J1.5
row1: D16.1 (K), D17.1 (K), D18.1 (K), D19.1 (K), D20.1 (K), D21.1 (K), D22.1 (K), D23.1 (K), D24.1 (K), D25.1 (K), D26.1 (K), D27.1 (K), D28.1 (K), D29.1 (K), D30.1 (K), J1.4
row2: D31.1 (K), D32.1 (K), D33.1 (K), D34.1 (K), D35.1 (K), D36.1 (K), D37.1 (K), D38.1 (K), D39.1 (K), D40.1 (K), D41.1 (K), D42.1 (K), D43.1 (K), D44.1 (K), D68.1 (K), J1.3
row3: D45.1 (K), D46.1 (K), D47.1 (K), D48.1 (K), D49.1 (K), D50.1 (K), D51.1 (K), D52.1 (K), D53.1 (K), D54.1 (K), D55.1 (K), D56.1 (K), D57.1 (K), D58.1 (K), J1.2
row 4: D59.1 (K), D60.1 (K), D61.1 (K), D62.1 (K), D63.1 (K), D64.1 (K), D65.1 (K), D66.1 (K), D67.1 (K), J1.1

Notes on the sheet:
rotaryENC
